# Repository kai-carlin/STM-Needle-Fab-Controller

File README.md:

# STM-Needle-Fab-Controller
College of Marin Physics Club Needle Fabrication Unit Controller Project

## What it is

STM tips are commonly made by electrochemically etching tungsten wire in sodium hydroxide. The wire necks down at the liquid surface until the lower section drops off, and the etching current falls abruptly. Etching that continues after the break blunts the tip, so the faster the current is cut, the sharper the tip. This project is an open, low-cost controller that detects the break and cuts the current in hardware, with a microcontroller for arming, display, alarm and logging.

## How it works

The cell current flows through a low-side switch and a small sense resistor to ground. The voltage across the sense resistor goes through an op-amp differentiator, which responds to the fast current drop at the break and largely ignores the slow decline before it. A fast latching comparator compares the differentiator output with an adjustable threshold and turns the switch off, and the latch holds that decision until it is reset. The cut-off path involves no firmware. A Teensy 4.1 sets the threshold, arms and resets the latch, drives the displays and buzzer, and can log the etching current.

## Operator interface

The front panel uses industrial-style controls on a small panel. Three five-digit seven-segment displays, driven over SPI by the Teensy, show the run time, the applied etch voltage, and the etching current. A Power toggle and a Solution Voltage toggle each have an indicator LED. Knobs adjust the etch voltage and the lowering and raising speeds of the wire stage, and pushbuttons cover Start, Abort, and manual raise and lower. They are read by the Teensy through pull-up inputs, and driven by the Teensy through MOSFETS

## Design choices

- **Low-side current sensing**, so the signal doesn't depend on the supply voltage or pick up its ripple.
- **A differentiator instead of a fixed current level**, because the current at drop-off varies with wire diameter and immersion depth.
- **A latch**, because the detector output is only a brief pulse.
- **Safe signal polarity**: switching the current on moves the detector away from its trip point, so a restart doesn't trigger it.
- **Quiet power**: linear regulators for the analog and etch rails, since switching noise looks like events to a high-gain differentiator. A buck converter is used only for the digital loads.

## Methods

**Simulation (KiCad).** A behavioral cell model with a slow current decline followed by a fast drop, plus noise sources, is used to sweep the edge speed and threshold. The goal is a detector that trips on the drop-off but not on noise or the decline.

**Measuring the real cell.** Before building the board, we plan to wire a bench supply, the cell and a 10 ohm sense resistor, and record the whole etch, the noise before the break, and the break itself with a single-shot oscilloscope trigger over several etches. The size and speed of the break, compared with the largest noise slope, decide whether the detector works and how to size it. The captured waveforms are then replayed in simulation.

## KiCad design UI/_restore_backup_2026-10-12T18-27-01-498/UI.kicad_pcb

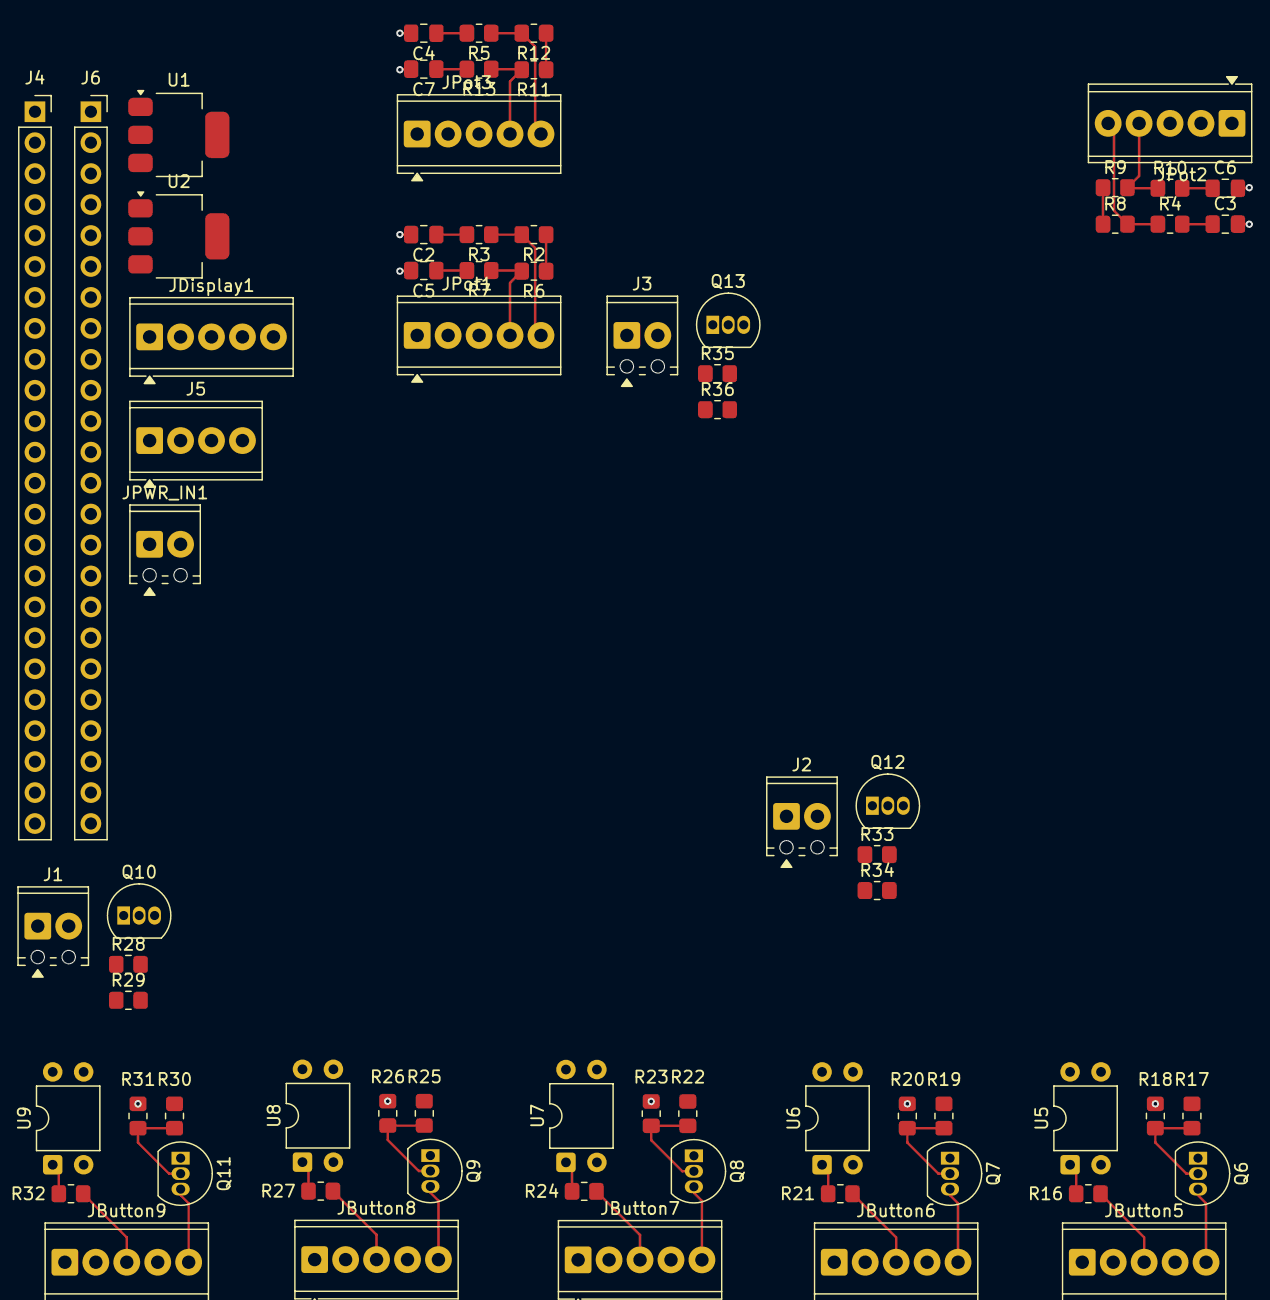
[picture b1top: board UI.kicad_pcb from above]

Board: 4 copper layers, 70 parts (0 on the bottom side), 43 nets.

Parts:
C2, C3, C4, C5, C6, C7: 0.01u; C_0805_2012Metric_Pad1.18x1.45mm_HandSolder
J1, J2, J3: Screw_Terminal_01x02; TerminalBlock_Phoenix_MPT-0,5-2-2.54_1x02_P2.54mm_Horizontal
J4, J6: Conn_01x24_Socket; PinSocket_1x24_P2.54mm_Vertical
J5: Screw_Terminal_01x04; TerminalBlock_Phoenix_MPT-0,5-4-2.54_1x04_P2.54mm_Horizontal
JButton5, JButton6, JButton7, JButton8, JButton9: Screw_Terminal_01x05; TerminalBlock_Phoenix_MPT-0,5-5-2.54_1x05_P2.54mm_Horizontal
JDisplay1: Screw_Terminal_01x05; TerminalBlock_Phoenix_MPT-0,5-5-2.54_1x05_P2.54mm_Horizontal
JPWR_IN1: Screw_Terminal_01x02; TerminalBlock_Phoenix_MPT-0,5-2-2.54_1x02_P2.54mm_Horizontal
JPot1, JPot2, JPot3: Screw_Terminal_01x05; TerminalBlock_Phoenix_MPT-0,5-5-2.54_1x05_P2.54mm_Horizontal
Q6, Q7, Q8, Q9, Q10, Q11, Q12, Q13: 2N7000; TO-92_Inline
R2, R3, R4, R5, R6, R7, R8, R9, R10, R11, R12, R13, R18, R20, R23, R26, R29, R31, R34, R36: 10k; R_0805_2012Metric_Pad1.20x1.40mm_HandSolder
R16, R21, R24, R27, R32: 1.2k; R_0805_2012Metric_Pad1.20x1.40mm_HandSolder
R17, R19, R22, R25, R28, R30, R33, R35: 100; R_0805_2012Metric_Pad1.20x1.40mm_HandSolder
U1: LD1117V50; SOT-223
U2: AMS1117-3.3; SOT-223-3_TabPin2
U5, U6, U7, U8, U9: PC817; DIP-4_W7.62mm

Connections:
+3.3V: R2.1, R6.1, R8.1, R9.1, R11.1, R12.1, U2.2 (VO)
+5V: JDisplay1.5, U1.2 (VO), U2.3 (VI)
+12V: J1.2, J2.2, J3.2, J5.4, JButton5.1, JButton5.4, JButton6.1, JButton6.4, JButton7.1, JButton7.4, JButton8.1, JButton8.4, JButton9.1, JButton9.4, JPWR_IN1.2
+~7V: J5.2, U1.3 (VI)
/Latching LED Button1/LED-: JButton5.5, Q6.3 (D)
/Latching LED Button1/NO: JButton5.3, R16.1
/Latching LED Button2/LED-: JButton6.5, Q7.3 (D)
/Latching LED Button2/NO: JButton6.3, R21.1
/Latching LED Button3/LED-: JButton7.5, Q8.3 (D)
/Latching LED Button3/NO: JButton7.3, R24.1
/Latching LED Button4/LED-: JButton8.5, Q9.3 (D)
/Latching LED Button4/NO: JButton8.3, R27.1
/Latching LED Button5/LED-: JButton9.5, Q11.3 (D)
/Latching LED Button5/NO: JButton9.3, R32.1
/Pilot Light1/LED-: J1.1, Q10.3 (D)
/Pilot Light2/LED-: J2.1, Q12.3 (D)
/Pilot Light3/LED-: J3.1, Q13.3 (D)
/ROT Reading1/Terminal_A: C2.1, R3.2
/ROT Reading1/Terminal_A_Raw: JPot1.5, R2.2, R3.1
/ROT Reading1/Terminal_B: C5.1, R7.2
/ROT Reading1/Terminal_B_Raw: JPot1.4, R6.2, R7.1
/ROT Reading2/Terminal_A: C3.1, R4.2
/ROT Reading2/Terminal_A_Raw: JPot2.5, R4.1, R8.2
/ROT Reading2/Terminal_B: C6.1, R10.2
/ROT Reading2/Terminal_B_Raw: JPot2.4, R9.2, R10.1
/ROT Reading3/Terminal_A: C4.1, R5.2
/ROT Reading3/Terminal_A_Raw: JPot3.5, R5.1, R12.2
/ROT Reading3/Terminal_B: C7.1, R13.2
/ROT Reading3/Terminal_B_Raw: JPot3.4, R11.2, R13.1
GND: C2.2, C3.2, C4.2, C5.2, C6.2, C7.2, J5.1, J5.3, JDisplay1.1, JPWR_IN1.1, JPot1.1, JPot1.3, JPot2.1, JPot2.3, JPot3.1, JPot3.3, Q6.1 (S), Q7.1 (S), Q8.1 (S), Q9.1 (S), Q10.1 (S), Q11.1 (S), Q12.1 (S), Q13.1 (S), R18.1, R20.1, R23.1, R26.1, R29.1, R31.1, R34.1, R36.1, U1.1 (GND), U2.1 (GND), U5.2, U5.3, U6.2, U6.3, U7.2, U7.3, U8.2, U8.3, U9.2, U9.3
unnamed: Q6.2 (G), R17.2, R18.2
unnamed: Q7.2 (G), R19.2, R20.2
unnamed: Q8.2 (G), R22.2, R23.2
unnamed: Q9.2 (G), R25.2, R26.2
unnamed: Q10.2 (G), R28.2, R29.2
unnamed: Q11.2 (G), R30.2, R31.2
unnamed: Q12.2 (G), R33.2, R34.2
unnamed: Q13.2 (G), R35.2, R36.2
unnamed: R16.2, U5.1
unnamed: R21.2, U6.1
unnamed: R24.2, U7.1
unnamed: R27.2, U8.1
unnamed: R32.2, U9.1

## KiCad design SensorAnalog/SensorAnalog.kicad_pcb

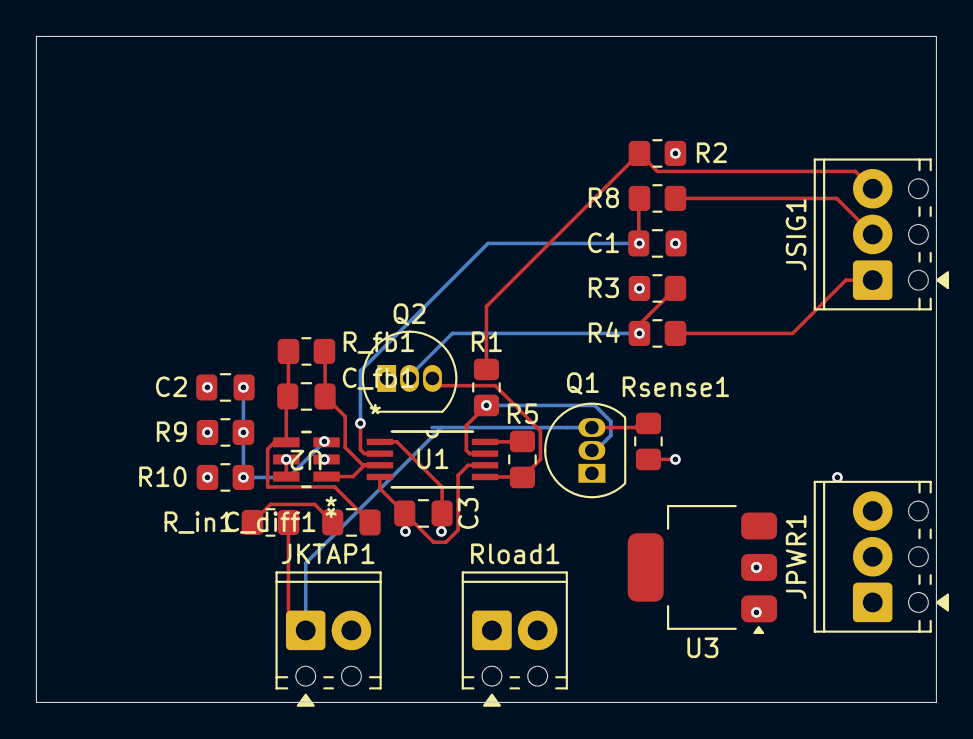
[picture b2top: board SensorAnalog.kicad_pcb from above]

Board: 4 copper layers, 50.0 x 37.0 mm, 25 parts (0 on the bottom side), 18 nets.

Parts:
C1: 10n; C_0805_2012Metric_Pad1.18x1.45mm_HandSolder
C2, C3: 1u; C_0805_2012Metric_Pad1.18x1.45mm_HandSolder
C_diff1: 100p; C_0805_2012Metric_Pad1.18x1.45mm_HandSolder
C_fb1: 4.7p; C_0805_2012Metric_Pad1.18x1.45mm_HandSolder
JKTAP1: Screw_Terminal_01x02; TerminalBlock_Phoenix_MPT-0,5-2-2.54_1x02_P2.54mm_Horizontal
JPWR1: Screw_Terminal_01x03; TerminalBlock_Phoenix_MPT-0,5-3-2.54_1x03_P2.54mm_Horizontal
JSIG1: Screw_Terminal_01x03; TerminalBlock_Phoenix_MPT-0,5-3-2.54_1x03_P2.54mm_Horizontal
Q1: BS170; TO-92_Inline
Q2: 2N7000; TO-92_Inline
R1, R3, R9, R10: 10k; R_0805_2012Metric_Pad1.20x1.40mm_HandSolder
R2: 33k; R_0805_2012Metric_Pad1.20x1.40mm_HandSolder
R4, R8: 1k; R_0805_2012Metric_Pad1.20x1.40mm_HandSolder
R5: 500; R_0805_2012Metric_Pad1.20x1.40mm_HandSolder
R_fb1: 15k; R_0805_2012Metric_Pad1.20x1.40mm_HandSolder
R_in1: 1k; R_0805_2012Metric_Pad1.20x1.40mm_HandSolder
Rload1: R='10/((0.0563 - 0.0513*min(max((time-500u)/20u, 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; TerminalBlock_Phoenix_MPT-0,5-2-2.54_1x02_P2.54mm_Horizontal
Rsense1: 10; R_0805_2012Metric_Pad1.20x1.40mm_HandSolder
U1: TL3016CPW; PW8
U2: OPA835IDBVR; DBV6
U3: LD1117V50; SOT-223

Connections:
0: C1.2, C2.1, C3.1, JKTAP1.2, JPWR1.3, Q2.1 (S), R2.1, R3.1, R9.2, Rsense1.2, U1.4 (VCC-), U1.6 (GND), U2.2 (VS-), U3.1 (GND)
/+5V: C3.2, R10.1, U1.1 (VCC+), U2.5 (*PD), U2.6 (VS+), U3.2 (VO)
/+~7V: JPWR1.2, U3.3 (VI)
/COMP_HAT: R5.2, U1.8 (*QOUT)
/COMP_OUT: Q1.2 (G), R1.1, U1.7 (QOUT)
/Etching_Pwr: JPWR1.1, Rload1.1
/GPIO_Reset: JSIG1.1, R4.2
/Latch: Q2.3 (D), R5.1, U1.5 (LATCHENABLE)
/OPA_INPUT: C2.2, R9.1, R10.2, U2.3 (VIN+)
/PIN_COMP_OUT: JSIG1.3, R1.2, R2.2
/SIGNAL_DIFF: C_fb1.1, R_fb1.1, U1.3 (IN-), U2.1 (VOUT)
/SIGNAL_DIV: JKTAP1.1, Q1.3 (S), R_in1.1, Rsense1.1
/UNFILTERED_Vref: JSIG1.2, R8.2
/Vref: C1.1, R8.1, U1.2 (IN+)
unnamed: C_diff1.1, R_in1.2
unnamed: Q1.1 (D), Rload1.2
unnamed: Q2.2 (G), R3.2, R4.1
unnamed: C_diff1.2, C_fb1.2, R_fb1.2, U2.4 (VIN-)
